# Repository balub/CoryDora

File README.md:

# CoryDora

A simple open-source, RP2040-based, QMK-compatible 3x3 mechanical macropad.

## Rationale

The main goal of this project is to have a cheap, easy-to-build, feature-rich numpad which is completely open source.

You can now buy the CoryDora yourself at the [Absurd Store](https://shop.absurd.industries/products/cory-dora).
Onboarding instructions are available [here](https://rowan-ninja-baa.notion.site/CoryDora-Onboarding-12d9d3177a9b8016bcddd6904b028f71).
Full build guide is available [here](https://rowan-ninja-baa.notion.site/CoryDora-v1-1-Build-Guide-cc727f8be312492a9d3bb8e5530b1656).

## Features:

- Easy to source and build components.
- Hot swappable keys.
- QMK compatible.
- OLED 0.91" screen.
- At least 1 rotary encoder
- Completely open-source.

## Parts list
**Part**|**Quantity**|**Link to buy online**
:-----:|:-----:|:-----:
 Hotswap Sockets|9|https://stackskb.com/store/ttc-pokayoke-hotswap-sockets-v2-10000-cycles
 Through hole 1N4148 Diode|9|https://stackskb.com/store/1n4148-through-hole-diode
 RP2040 zero|1|https://robu.in/product/waveshare-rp2040-zero-without-header
 Rotary Encoders|1|https://robu.in/product/m274-360-degree-rotary-encoder-module-brick-sensor/
 0.91 inch I2C OLED display|1|https://robu.in/product/0-91-inch-128x32-i2c-iic-serial-oled-lcd-display-modulewith-gn
 Mx compatible mechanical switches|9|https://stackskb.com/product-category/switches/linear/

## Firmware

Clone [forked QMK](https://github.com/balub/qmk_firmware) repositories and set up the build environment. See the [build environment setup](https://docs.qmk.fm/#/getting_started_build_tools) and the [make instructions](https://docs.qmk.fm/#/getting_started_make_guide) for more information. Brand new to QMK? Start with our [Complete Newbs Guide](https://docs.qmk.fm/#/newbs).

## License

Original CoryDora hardware designs and accompanying documentation are licensed
under **CERN-OHL-S-2.0**. You may use, modify, manufacture, and sell the hardware
under its terms. Retain the project attribution and other applicable notices;
provide the complete editable sources under the same licence when required
for distributed derivatives.

See [licensing scope and third-party exclusions](LICENSE) and the
[complete licence text](LICENSES/CERN-OHL-S-2.0.txt). Third-party material retains
its existing licences. The [separate QMK firmware fork](https://github.com/balub/qmk_firmware)
retains its applicable upstream and file-specific licences.

Attribution: **CoryDora project and its contributors**.
Source location: <https://github.com/balub/CoryDora>.

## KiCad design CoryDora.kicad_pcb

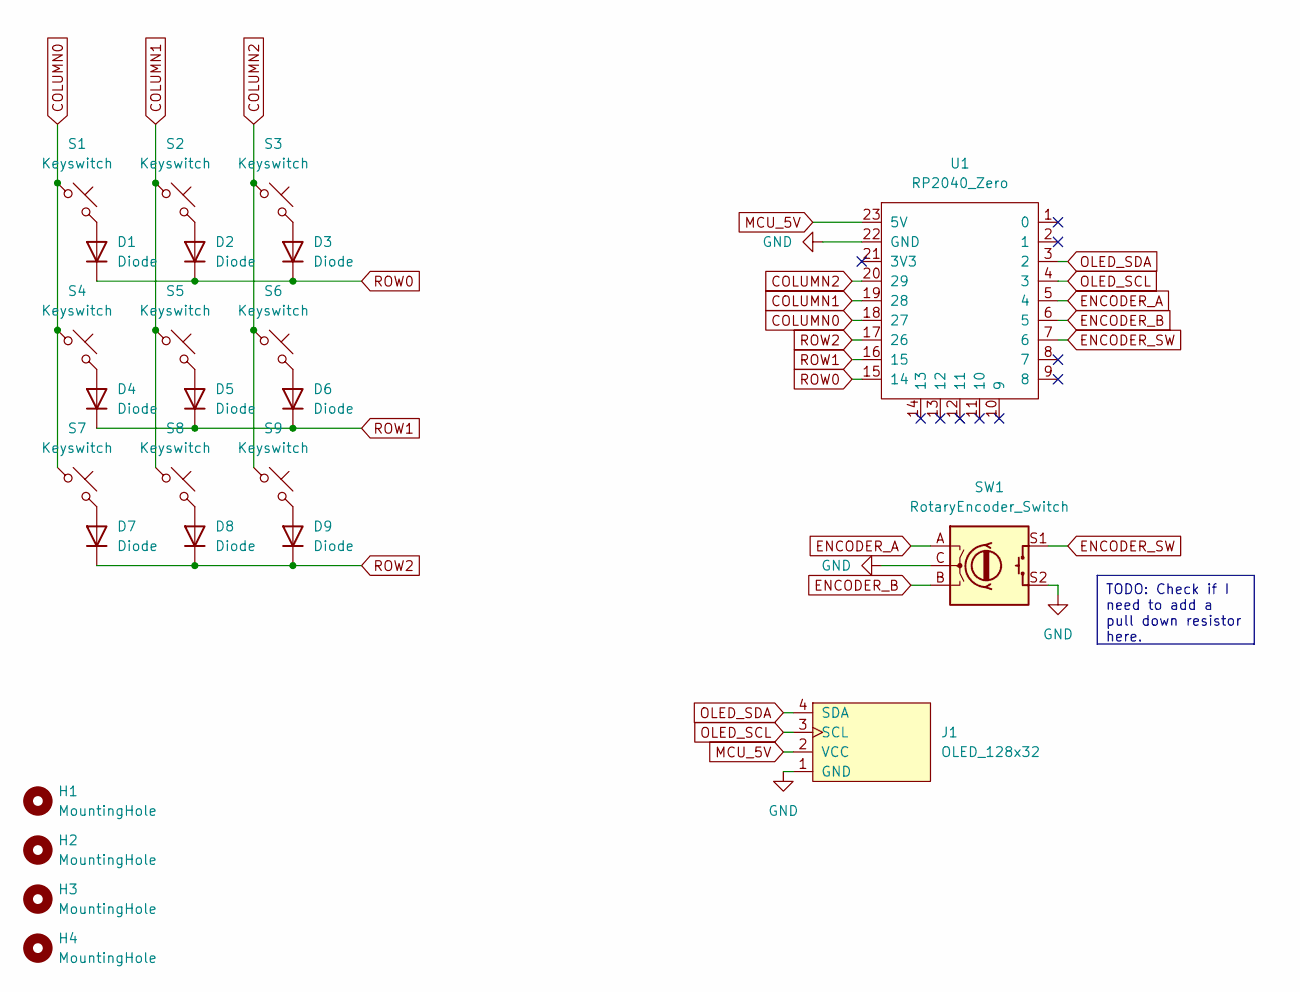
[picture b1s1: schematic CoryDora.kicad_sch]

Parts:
D1, D2, D3, D4, D5, D6, D7, D8, D9: Diode; Diode_DO-35
H1, H2, H3, H4: MountingHole; MountingHole_2.2mm_M2
J1: OLED_128x32
S1, S2, S3, S4, S5, S6, S7, S8, S9: Keyswitch; Hotswap_MX_Plated_1.00u
SW1: RotaryEncoder_Switch; RotaryEncoder_Alps_EC11E-Switch_Vertical_H20mm
U1: RP2040_Zero

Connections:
COLUMN0: S1.1, S4.1, S7.1, U1.18 (27)
COLUMN1: S2.1, S5.1, S8.1, U1.19 (28)
COLUMN2: S3.1, S6.1, S9.1, U1.20 (29)
ENCODER_A: SW1.A, U1.5 (4)
ENCODER_B: SW1.B, U1.6 (5)
ENCODER_SW: SW1.S1, U1.7 (6)
GND: J1.1 (GND), SW1.C, SW1.S2, U1.22 (GND)
MCU_5V: J1.2 (VCC), U1.23 (5V)
unnamed: D1.2 (A), S1.2
unnamed: D2.2 (A), S2.2
unnamed: D3.2 (A), S3.2
unnamed: D4.2 (A), S4.2
unnamed: D5.2 (A), S5.2
unnamed: D6.2 (A), S6.2
unnamed: D7.2 (A), S7.2
unnamed: D8.2 (A), S8.2
unnamed: D9.2 (A), S9.2
OLED_SCL: J1.3 (SCL), U1.4 (3)
OLED_SDA: J1.4 (SDA), U1.3 (2)
ROW0: D1.1 (K), D2.1 (K), D3.1 (K), U1.15 (14)
ROW1: D4.1 (K), D5.1 (K), D6.1 (K), U1.16 (15)
ROW2: D7.1 (K), D8.1 (K), D9.1 (K), U1.17 (26)

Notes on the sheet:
TODO: Check if I need to add a pull down resistor here.

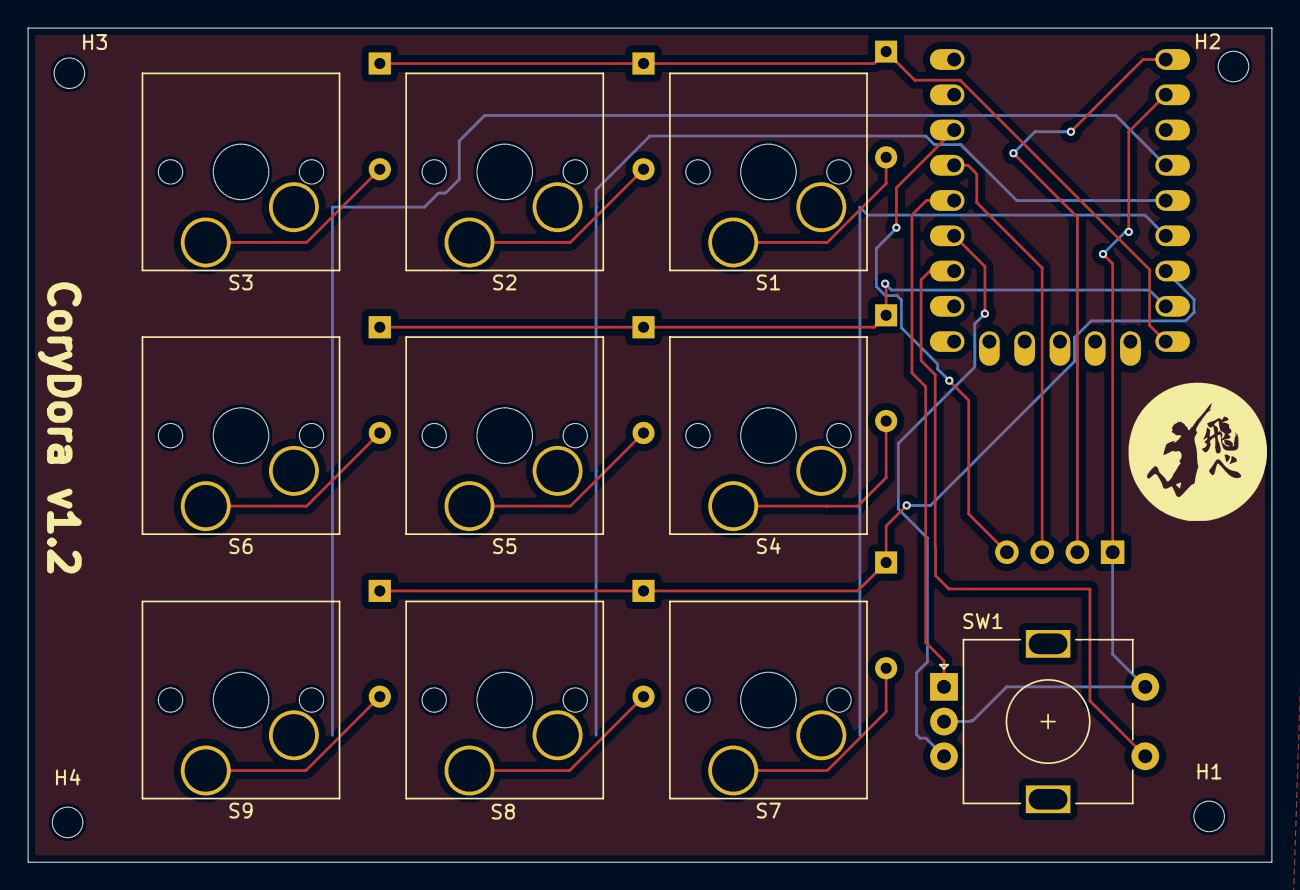
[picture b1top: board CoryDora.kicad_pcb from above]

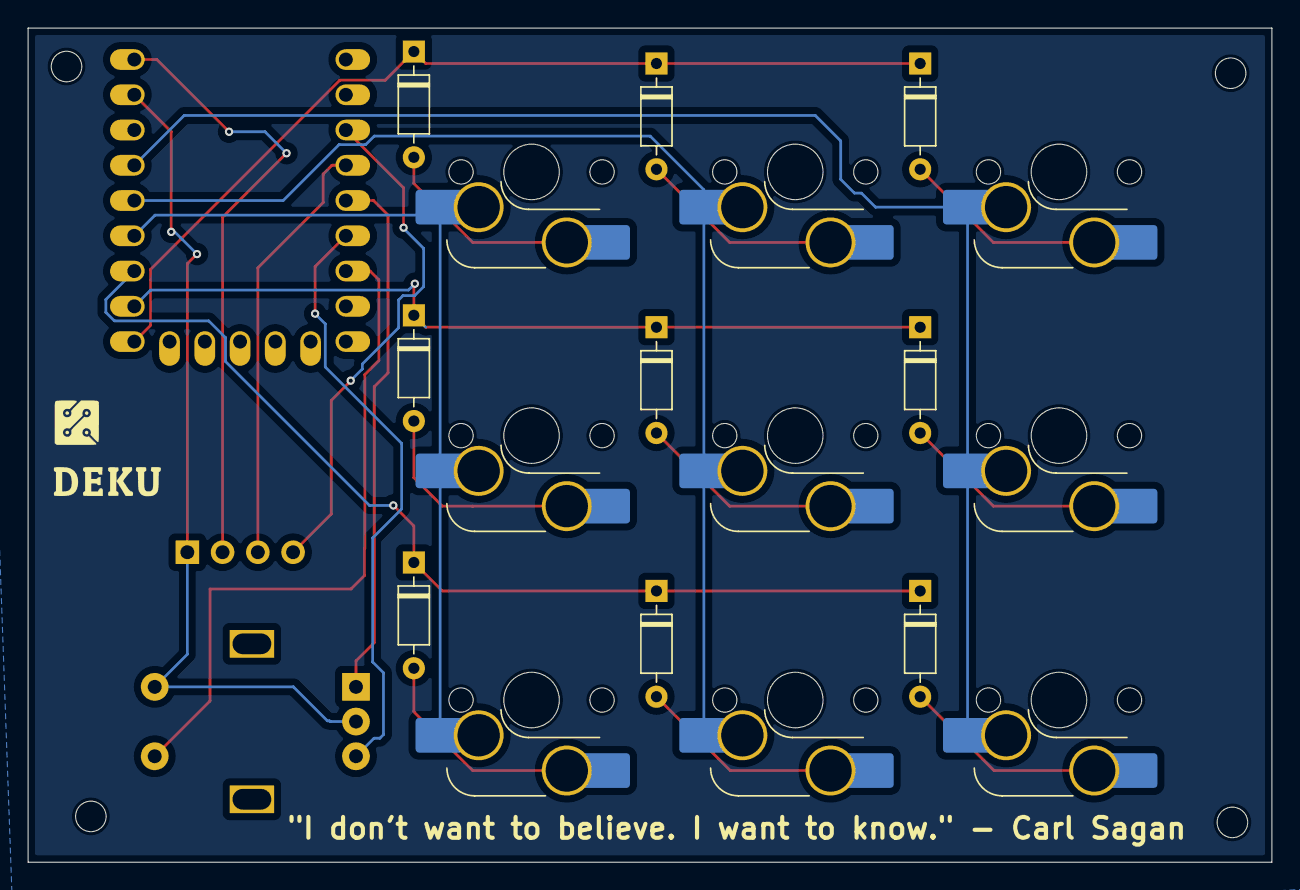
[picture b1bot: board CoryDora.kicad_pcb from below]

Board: 2 copper layers, 89.6 x 60.1 mm, 25 parts (10 on the bottom side), 22 nets.

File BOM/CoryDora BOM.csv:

"Reference","Value","Datasheet","Footprint","Qty","DNP"
"D1,D2,D3,D4,D5,D6,D7,D8,D9","Diode","","ScottoKeebs_Components:Diode_DO-35","9",""
"H1,H2,H3,H4","MountingHole","~","MountingHole:MountingHole_2.2mm_M2","4",""
"J1","OLED_128x32","","ScottoKeebs_Components:OLED_128x32","1",""
"S1,S2,S3,S4,S5,S6,S7,S8,S9","Keyswitch","~","ScottoKeebs_Hotswap:Hotswap_MX_Plated_1.00u","9",""
"SW1","RotaryEncoder_Switch","~","Rotary_Encoder:RotaryEncoder_Alps_EC11E-Switch_Vertical_H20mm","1",""
"U1","RP2040_Zero","","ScottoKeebs_MCU:RP2040_Zero","1",""

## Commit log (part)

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2024-03-07 feat: base schematic complete
2024-03-07 chore: complete layout in PCB editor
2024-03-12 chore: completed PCB design
2024-03-12 chore: removed unimportant texts from silkscreen
2024-03-12 chore: added text and graphics to silkscreen
2024-03-15 chore: added a simple readme for project
2024-03-15 chore: added assets to project
2024-03-15 chore: added open hardware label to project
2024-04-05 feat: added case stl and step files
2024-04-05 chore: added files to gitignore
2024-04-06 chore: added image to readme
2024-04-06 chore: updated readme
2024-04-20 chore: fixed issue in partlist table
2024-06-11 chore: made modifications for v1.1
2024-08-21 chore: added front and bottom copper fill
2024-09-06 feat: added v1.2 case design
2024-09-20 chore: added CoryDora schematic
2024-10-04 chore: added v1.2 case and PCB step files
2024-10-04 chore: modified readme file
2024-10-25 Update README.md
    Updated the spec!
2024-10-28 chore: modified readme
